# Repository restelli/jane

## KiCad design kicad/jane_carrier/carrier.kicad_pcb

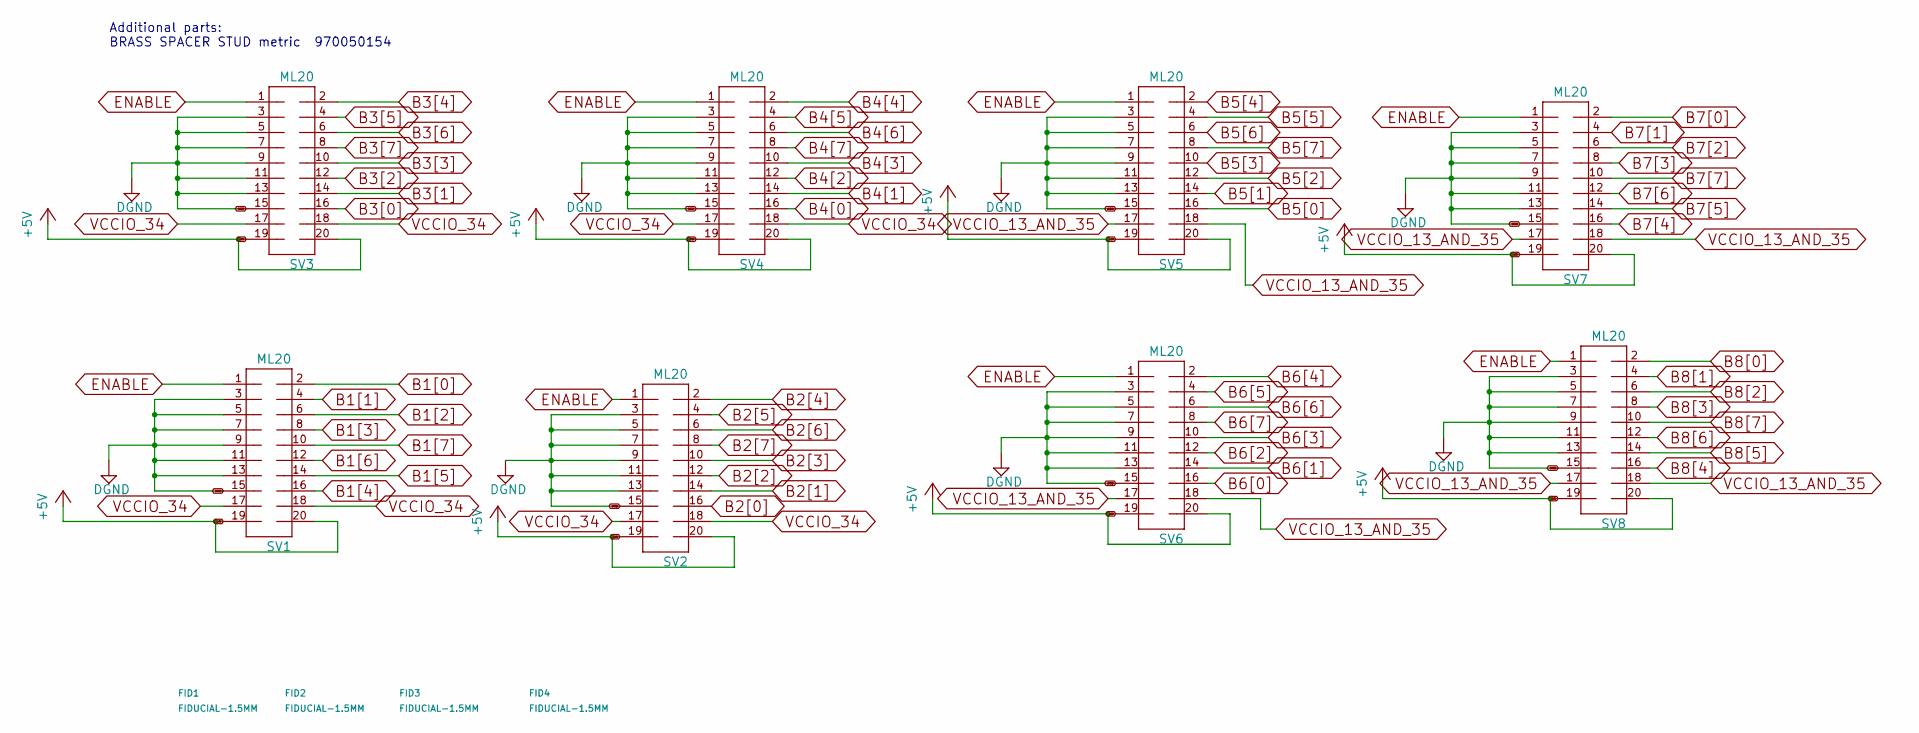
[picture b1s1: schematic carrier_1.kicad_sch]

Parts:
FID1, FID2, FID3, FID4: FIDUCIAL-1.5MM; FID_1.5MM
SV1, SV2, SV3, SV4, SV5, SV6, SV7, SV8: ML20; PARTNO 302-S201; DIGIKEY ED10524-ND

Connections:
+5V: SV1.19, SV1.20, SV2.19, SV2.20, SV3.19, SV3.20, SV4.19, SV4.20, SV5.19, SV5.20, SV6.19, SV6.20, SV7.19, SV7.20, SV8.19, SV8.20; also elsewhere on the board
B1[0]: SV1.2; also elsewhere on the board
B1[1]: SV1.4; also elsewhere on the board
B1[2]: SV1.6; also elsewhere on the board
B1[3]: SV1.8; also elsewhere on the board
B1[4]: SV1.16; also elsewhere on the board
B1[5]: SV1.14; also elsewhere on the board
B1[6]: SV1.12; also elsewhere on the board
B1[7]: SV1.10; also elsewhere on the board
B2[0]: SV2.16; also elsewhere on the board
B2[1]: SV2.14; also elsewhere on the board
B2[2]: SV2.12; also elsewhere on the board
B2[3]: SV2.10; also elsewhere on the board
B2[4]: SV2.2; also elsewhere on the board
B2[5]: SV2.4; also elsewhere on the board
B2[6]: SV2.6; also elsewhere on the board
B2[7]: SV2.8; also elsewhere on the board
B3[0]: SV3.16; also elsewhere on the board
B3[1]: SV3.14; also elsewhere on the board
B3[2]: SV3.12; also elsewhere on the board
B3[3]: SV3.10; also elsewhere on the board
B3[4]: SV3.2; also elsewhere on the board
B3[5]: SV3.4; also elsewhere on the board
B3[6]: SV3.6; also elsewhere on the board
B3[7]: SV3.8; also elsewhere on the board
B4[0]: SV4.16; also elsewhere on the board
B4[1]: SV4.14; also elsewhere on the board
B4[2]: SV4.12; also elsewhere on the board
B4[3]: SV4.10; also elsewhere on the board
B4[4]: SV4.2; also elsewhere on the board
B4[5]: SV4.4; also elsewhere on the board
B4[6]: SV4.6; also elsewhere on the board
B4[7]: SV4.8; also elsewhere on the board
B5[0]: SV5.16; also elsewhere on the board
B5[1]: SV5.14; also elsewhere on the board
B5[2]: SV5.12; also elsewhere on the board
B5[3]: SV5.10; also elsewhere on the board
B5[4]: SV5.2; also elsewhere on the board
B5[5]: SV5.4; also elsewhere on the board
B5[6]: SV5.6; also elsewhere on the board
B5[7]: SV5.8; also elsewhere on the board
B6[0]: SV6.16; also elsewhere on the board
B6[1]: SV6.14; also elsewhere on the board
B6[2]: SV6.12; also elsewhere on the board
B6[3]: SV6.10; also elsewhere on the board
B6[4]: SV6.2; also elsewhere on the board
B6[5]: SV6.4; also elsewhere on the board
B6[6]: SV6.6; also elsewhere on the board
B6[7]: SV6.8; also elsewhere on the board
B7[0]: SV7.2; also elsewhere on the board
B7[1]: SV7.4; also elsewhere on the board
B7[2]: SV7.6; also elsewhere on the board
B7[3]: SV7.8; also elsewhere on the board
B7[4]: SV7.16; also elsewhere on the board
B7[5]: SV7.14; also elsewhere on the board
B7[6]: SV7.12; also elsewhere on the board
B7[7]: SV7.10; also elsewhere on the board
B8[0]: SV8.2; also elsewhere on the board
B8[1]: SV8.4; also elsewhere on the board
B8[2]: SV8.6; also elsewhere on the board
B8[3]: SV8.8; also elsewhere on the board
B8[4]: SV8.16; also elsewhere on the board
B8[5]: SV8.14; also elsewhere on the board
B8[6]: SV8.12; also elsewhere on the board
B8[7]: SV8.10; also elsewhere on the board
DGND: SV1.3, SV1.5, SV1.7, SV1.9, SV1.11, SV1.13, SV1.15, SV2.3, SV2.5, SV2.7, SV2.9, SV2.11, SV2.13, SV2.15, SV3.3, SV3.5, SV3.7, SV3.9, SV3.11, SV3.13, SV3.15, SV4.3, SV4.5, SV4.7, SV4.9, SV4.11, SV4.13, SV4.15, SV5.3, SV5.5, SV5.7, SV5.9, SV5.11, SV5.13, SV5.15, SV6.3, SV6.5, SV6.7, SV6.9, SV6.11, SV6.13, SV6.15, SV7.3, SV7.5, SV7.7, SV7.9, SV7.11, SV7.13, SV7.15, SV8.3, SV8.5, SV8.7, SV8.9, SV8.11, SV8.13, SV8.15; also elsewhere on the board
ENABLE: SV1.1, SV2.1, SV3.1, SV4.1, SV5.1, SV6.1, SV7.1, SV8.1; also elsewhere on the board
VCCIO_13_AND_35: SV5.17, SV5.18, SV6.17, SV6.18, SV7.17, SV7.18, SV8.17, SV8.18; also elsewhere on the board
VCCIO_34: SV1.17, SV1.18, SV2.17, SV2.18, SV3.17, SV3.18, SV4.17, SV4.18; also elsewhere on the board

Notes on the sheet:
Additional parts: BRASS SPACER STUD metric 970050154

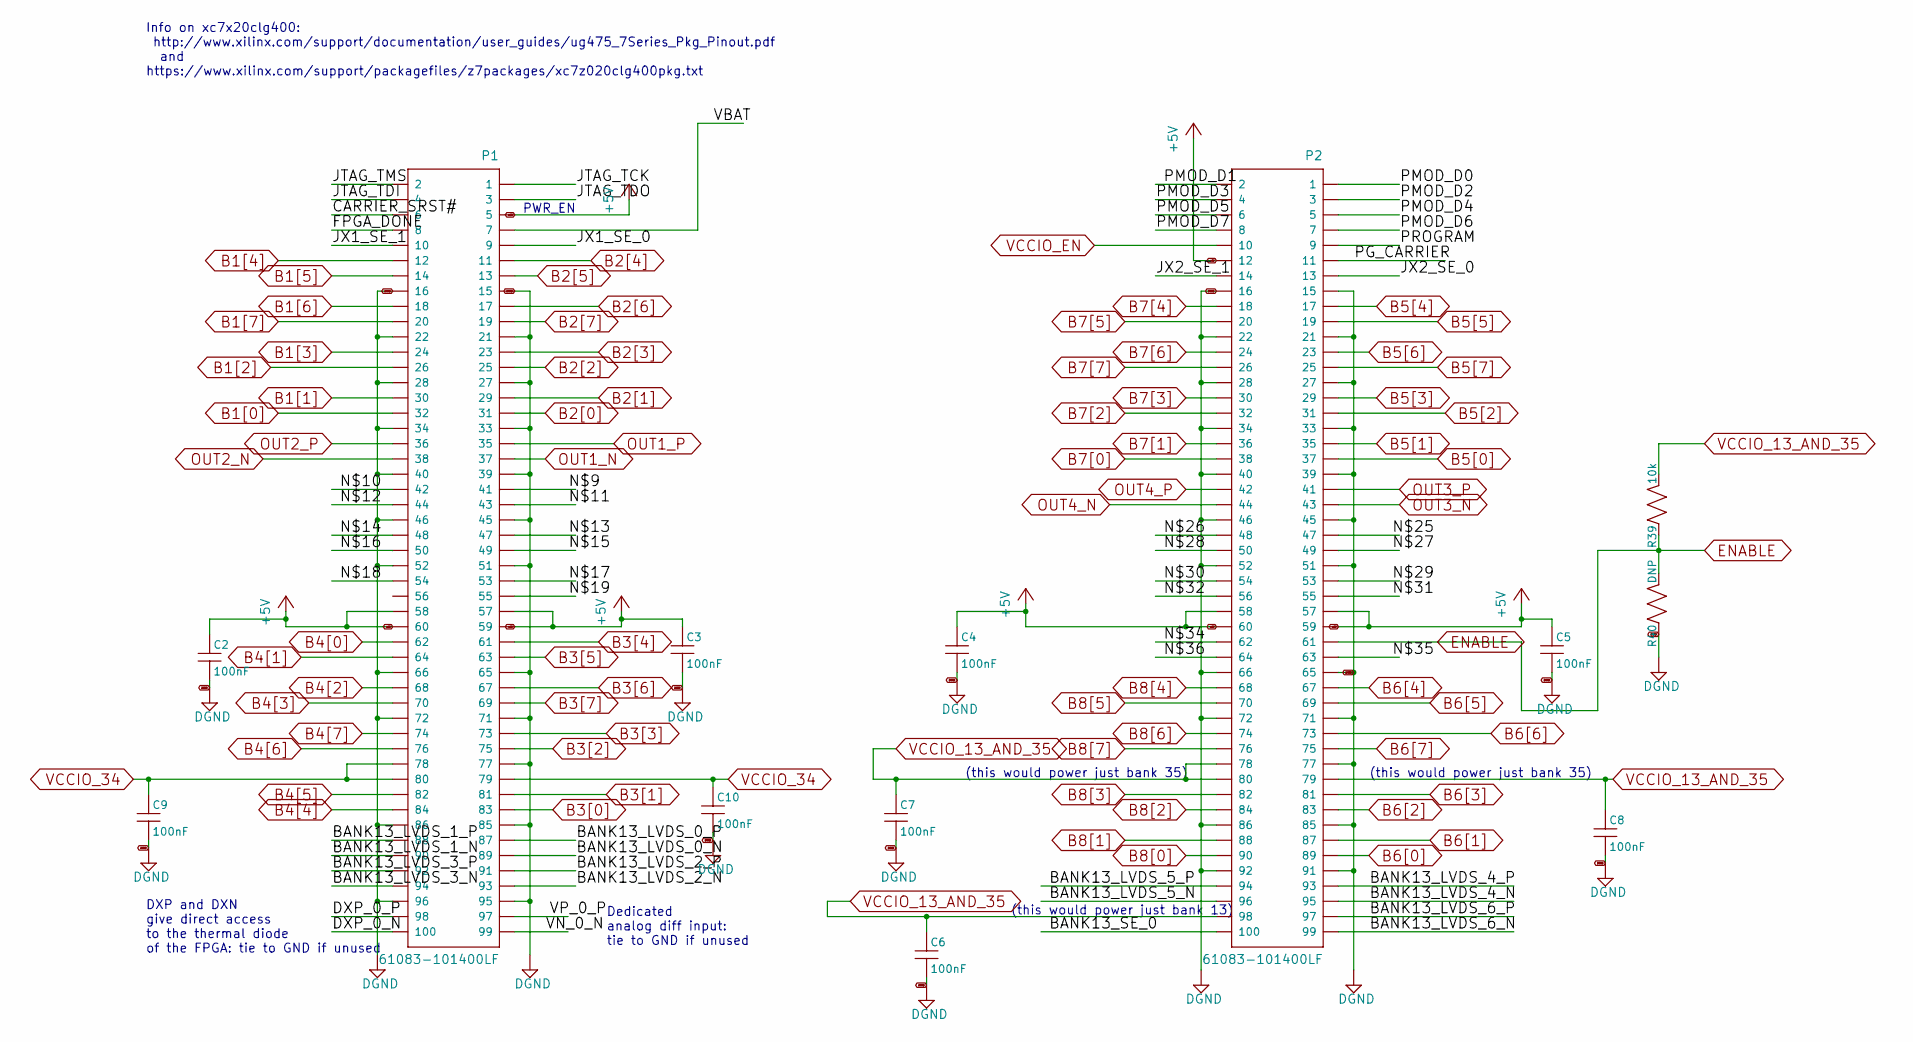
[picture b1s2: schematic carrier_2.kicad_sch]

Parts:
C2, C3, C4, C5, C6, C7, C8, C9, C10: 100nF; C_MLCC_0603; PARTNO AVX 06035C104K4T2A
P1, P2: 61083-101400LF; FCI_61083-101400LF; PARTNO 61083-101400LF
R39: 10k; R_0603; PARTNO ERA-3AED103V
R40: DNP; R_0603

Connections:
+5V: C2.P$1 (1), C3.P$1 (1), C4.P$1 (1), C5.P$1 (1), P1.5, P1.57, P1.58, P1.59, P1.60, P2.12, P2.57, P2.58, P2.59, P2.60; also elsewhere on the board
/carrier_2/BANK13_LVDS_0_N: P1.89
/carrier_2/BANK13_LVDS_0_P: P1.87
/carrier_2/BANK13_LVDS_1_N: P1.90
/carrier_2/BANK13_LVDS_1_P: P1.88
/carrier_2/BANK13_LVDS_2_N: P1.93
/carrier_2/BANK13_LVDS_2_P: P1.91
/carrier_2/BANK13_LVDS_3_N: P1.94
/carrier_2/BANK13_LVDS_3_P: P1.92
/carrier_2/BANK13_LVDS_4_N: P2.95
/carrier_2/BANK13_LVDS_4_P: P2.93
/carrier_2/BANK13_LVDS_5_N: P2.96
/carrier_2/BANK13_LVDS_5_P: P2.94
/carrier_2/BANK13_LVDS_6_N: P2.99
/carrier_2/BANK13_LVDS_6_P: P2.97
/carrier_2/BANK13_SE_0: P2.100
/carrier_2/CARRIER_SRST#: P1.6
/carrier_2/DXP_0_N: P1.100
/carrier_2/DXP_0_P: P1.98
/carrier_2/FPGA_DONE: P1.8
/carrier_2/JTAG_TCK: P1.1
/carrier_2/JTAG_TDI: P1.4
/carrier_2/JTAG_TDO: P1.3
/carrier_2/JTAG_TMS: P1.2
/carrier_2/JX1_SE_0: P1.9
/carrier_2/JX1_SE_1: P1.10
/carrier_2/JX2_SE_0: P2.13
/carrier_2/JX2_SE_1: P2.14
/carrier_2/N$9: P1.41
/carrier_2/N$10: P1.42
/carrier_2/N$11: P1.43
/carrier_2/N$12: P1.44
/carrier_2/N$13: P1.47
/carrier_2/N$14: P1.48
/carrier_2/N$15: P1.49
/carrier_2/N$16: P1.50
/carrier_2/N$17: P1.53
/carrier_2/N$18: P1.54
/carrier_2/N$19: P1.55
/carrier_2/N$25: P2.47
/carrier_2/N$26: P2.48
/carrier_2/N$27: P2.49
/carrier_2/N$28: P2.50
/carrier_2/N$29: P2.53
/carrier_2/N$30: P2.54
/carrier_2/N$31: P2.55
/carrier_2/N$32: P2.56
/carrier_2/N$34: P2.62
/carrier_2/N$35: P2.63
/carrier_2/N$36: P2.64
/carrier_2/PG_CARRIER: P2.11
/carrier_2/PMOD_D0: P2.1
/carrier_2/PMOD_D1: P2.2
/carrier_2/PMOD_D2: P2.3
/carrier_2/PMOD_D3: P2.4
/carrier_2/PMOD_D4: P2.5
/carrier_2/PMOD_D5: P2.6
/carrier_2/PMOD_D6: P2.7
/carrier_2/PMOD_D7: P2.8
/carrier_2/PROGRAM: P2.9
/carrier_2/VBAT: P1.7
/carrier_2/VN_0_N: P1.99
/carrier_2/VP_0_P: P1.97
B1[0]: P1.32; also elsewhere on the board
B1[1]: P1.30; also elsewhere on the board
B1[2]: P1.26; also elsewhere on the board
B1[3]: P1.24; also elsewhere on the board
B1[4]: P1.12; also elsewhere on the board
B1[5]: P1.14; also elsewhere on the board
B1[6]: P1.18; also elsewhere on the board
B1[7]: P1.20; also elsewhere on the board
B2[0]: P1.31; also elsewhere on the board
B2[1]: P1.29; also elsewhere on the board
B2[2]: P1.25; also elsewhere on the board
B2[3]: P1.23; also elsewhere on the board
B2[4]: P1.11; also elsewhere on the board
B2[5]: P1.13; also elsewhere on the board
B2[6]: P1.17; also elsewhere on the board
B2[7]: P1.19; also elsewhere on the board
B3[0]: P1.83; also elsewhere on the board
B3[1]: P1.81; also elsewhere on the board
B3[2]: P1.75; also elsewhere on the board
B3[3]: P1.73; also elsewhere on the board
B3[4]: P1.61; also elsewhere on the board
B3[5]: P1.63; also elsewhere on the board
B3[6]: P1.67; also elsewhere on the board
B3[7]: P1.69; also elsewhere on the board
B4[0]: P1.62; also elsewhere on the board
B4[1]: P1.64; also elsewhere on the board
B4[2]: P1.68; also elsewhere on the board
B4[3]: P1.70; also elsewhere on the board
B4[4]: P1.84; also elsewhere on the board
B4[5]: P1.82; also elsewhere on the board
B4[6]: P1.76; also elsewhere on the board
B4[7]: P1.74; also elsewhere on the board
B5[0]: P2.37; also elsewhere on the board
B5[1]: P2.35; also elsewhere on the board
B5[2]: P2.31; also elsewhere on the board
B5[3]: P2.29; also elsewhere on the board
B5[4]: P2.17; also elsewhere on the board
B5[5]: P2.19; also elsewhere on the board
B5[6]: P2.23; also elsewhere on the board
B5[7]: P2.25; also elsewhere on the board
B6[0]: P2.89; also elsewhere on the board
B6[1]: P2.87; also elsewhere on the board
B6[2]: P2.83; also elsewhere on the board
B6[3]: P2.81; also elsewhere on the board
B6[4]: P2.67; also elsewhere on the board
B6[5]: P2.69; also elsewhere on the board
B6[6]: P2.73; also elsewhere on the board
B6[7]: P2.75; also elsewhere on the board
B7[0]: P2.38; also elsewhere on the board
B7[1]: P2.36; also elsewhere on the board
B7[2]: P2.32; also elsewhere on the board
B7[3]: P2.30; also elsewhere on the board
B7[4]: P2.18; also elsewhere on the board
B7[5]: P2.20; also elsewhere on the board
B7[6]: P2.24; also elsewhere on the board
B7[7]: P2.26; also elsewhere on the board
B8[0]: P2.90; also elsewhere on the board
B8[1]: P2.88; also elsewhere on the board
B8[2]: P2.84; also elsewhere on the board
B8[3]: P2.82; also elsewhere on the board
B8[4]: P2.68; also elsewhere on the board
B8[5]: P2.70; also elsewhere on the board
B8[6]: P2.74; also elsewhere on the board
B8[7]: P2.76; also elsewhere on the board
DGND: C2.P$2 (2), C3.P$2 (2), C4.P$2 (2), C5.P$2 (2), C6.P$2 (2), C7.P$2 (2), C8.P$2 (2), C9.P$2 (2), C10.P$2 (2), P1.15, P1.16, P1.21, P1.22, P1.27, P1.28, P1.33, P1.34, P1.39, P1.40, P1.45, P1.46, P1.51, P1.52, P1.65, P1.66, P1.71, P1.72, P1.77, P1.85, P1.86, P1.95, P1.96, P2.15, P2.16, P2.21, P2.22, P2.27, P2.28, P2.33, P2.34, P2.39, P2.40, P2.45, P2.46, P2.51, P2.52, P2.65, P2.66, P2.71, P2.72, P2.77, P2.85, P2.86, P2.91, P2.92, R40.P$1 (1); also elsewhere on the board
ENABLE: P2.61, R39.P$1 (1), R40.P$2 (2); also elsewhere on the board
OUT1_N: P1.37; also elsewhere on the board
OUT1_P: P1.35; also elsewhere on the board
OUT2_N: P1.38; also elsewhere on the board
OUT2_P: P1.36; also elsewhere on the board
OUT3_N: P2.43; also elsewhere on the board
OUT3_P: P2.41; also elsewhere on the board
OUT4_N: P2.44; also elsewhere on the board
OUT4_P: P2.42; also elsewhere on the board
VCCIO_13_AND_35: C6.P$1 (1), C7.P$1 (1), C8.P$1 (1), P2.78, P2.79, P2.80, P2.98, R39.P$2 (2); also elsewhere on the board
VCCIO_34: C9.P$1 (1), C10.P$1 (1), P1.78, P1.79, P1.80; also elsewhere on the board
VCCIO_EN: P2.10; also elsewhere on the board

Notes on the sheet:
Dedicated analog diff input: tie to GND if unused
(this would power just bank 13)
(this would power just bank 35)
DXP and DXN give direct access to the thermal diode of the FPGA: tie to GND if unused
Info on xc7x20clg400: http://www.xilinx.com/support/documentation/user_guides/ug475_7Series_Pkg_Pinout.pdf and https://www.xilinx.com/support/packagefiles/z7packages/xc7z020clg400pkg.txt
PWR_EN

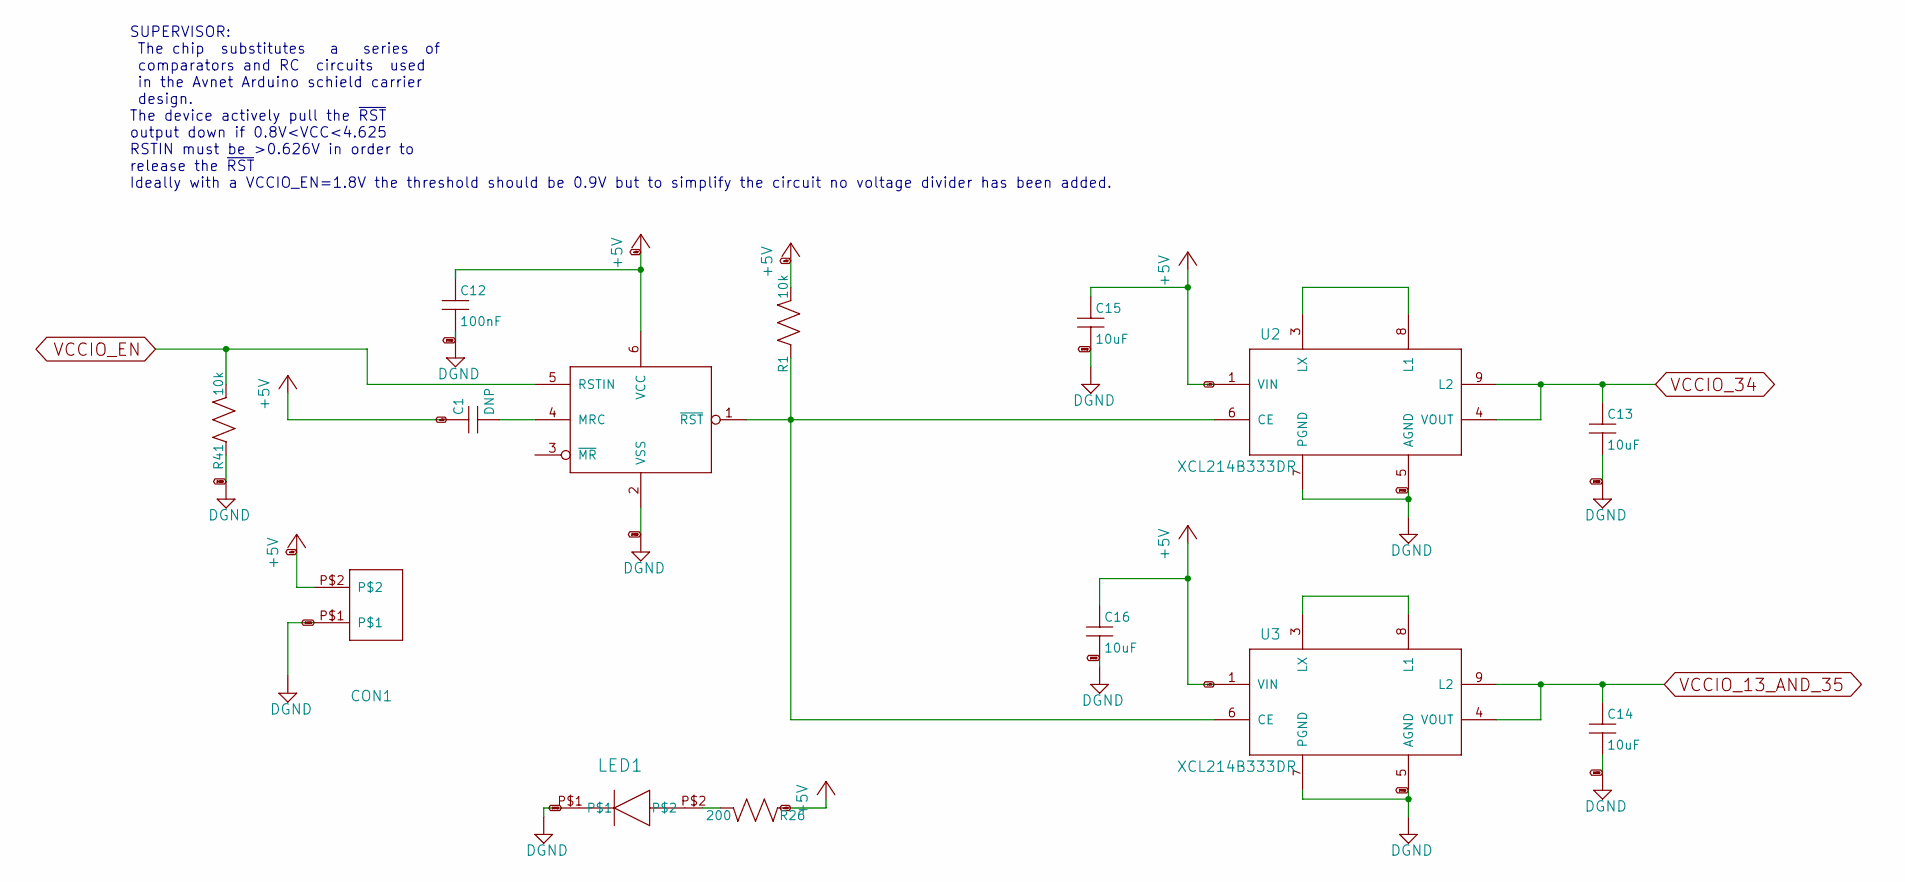
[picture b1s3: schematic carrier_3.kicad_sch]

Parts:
C1: DNP; C_MLCC_0603
C12: 100nF; C_MLCC_0603; PARTNO AVX 06035C104K4T2A
C13, C14, C15, C16: 10uF; C_MLCC_1210; PARTNO TDK C3225X5R1E106K250AA
CON1: EDSTL130_02
LED1: LED-AA4040QBS; PARTNO AA4040QBS/D
R1, R41: 10k; R_0603; PARTNO ERA-3AED103V
R26: 200; R_0603; PARTNO CRCW0603200RFKEA
U1: STM6779LWB6F; SOT95P280X145-6N; PARTNO STM6779LWB6F; DIGIKEY 497-8008-1-ND
U2, U3: XCL214B333DR; TOREX_XCL214B123DR; PARTNO XCL214B333DR; DIGIKEY 893-1218-1-ND

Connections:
+5V: C1.P$1 (1), C12.P$1 (1), C15.P$1 (1), C16.P$1 (1), CON1.P$2, R1.P$2 (2), R26.P$1 (1), U1.6 (VCC), U2.1 (VIN), U3.1 (VIN); also elsewhere on the board
DGND: C12.P$2 (2), C13.P$2 (2), C14.P$2 (2), C15.P$2 (2), C16.P$2 (2), CON1.P$1, LED1.P$1, R41.P$1 (1), U1.2 (VSS), U2.5 (AGND), U2.7 (PGND), U3.5 (AGND), U3.7 (PGND); also elsewhere on the board
unnamed: C1.P$2 (2), U1.4 (MRC)
unnamed: LED1.P$2, R26.P$2 (2)
unnamed: R1.P$1 (1), U1.1 (~RST), U2.6 (CE), U3.6 (CE)
unnamed: U2.3 (LX), U2.8 (L1)
unnamed: U3.3 (LX), U3.8 (L1)
VCCIO_13_AND_35: C14.P$1 (1), U3.4 (VOUT), U3.9 (L2); also elsewhere on the board
VCCIO_34: C13.P$1 (1), U2.4 (VOUT), U2.9 (L2); also elsewhere on the board
VCCIO_EN: R41.P$2 (2), U1.5 (RSTIN); also elsewhere on the board

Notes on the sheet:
SUPERVISOR: The chip substitutes a series of comparators and RC circuits used in the Avnet Arduino schield carrier design. The device actively pull the ~{RST} output down if 0.8V<VCC<4.625 RSTIN must be >0.626V in order to release the ~{RST} Ideally with a VCCIO_EN=1.8V the threshold should be 0.9V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

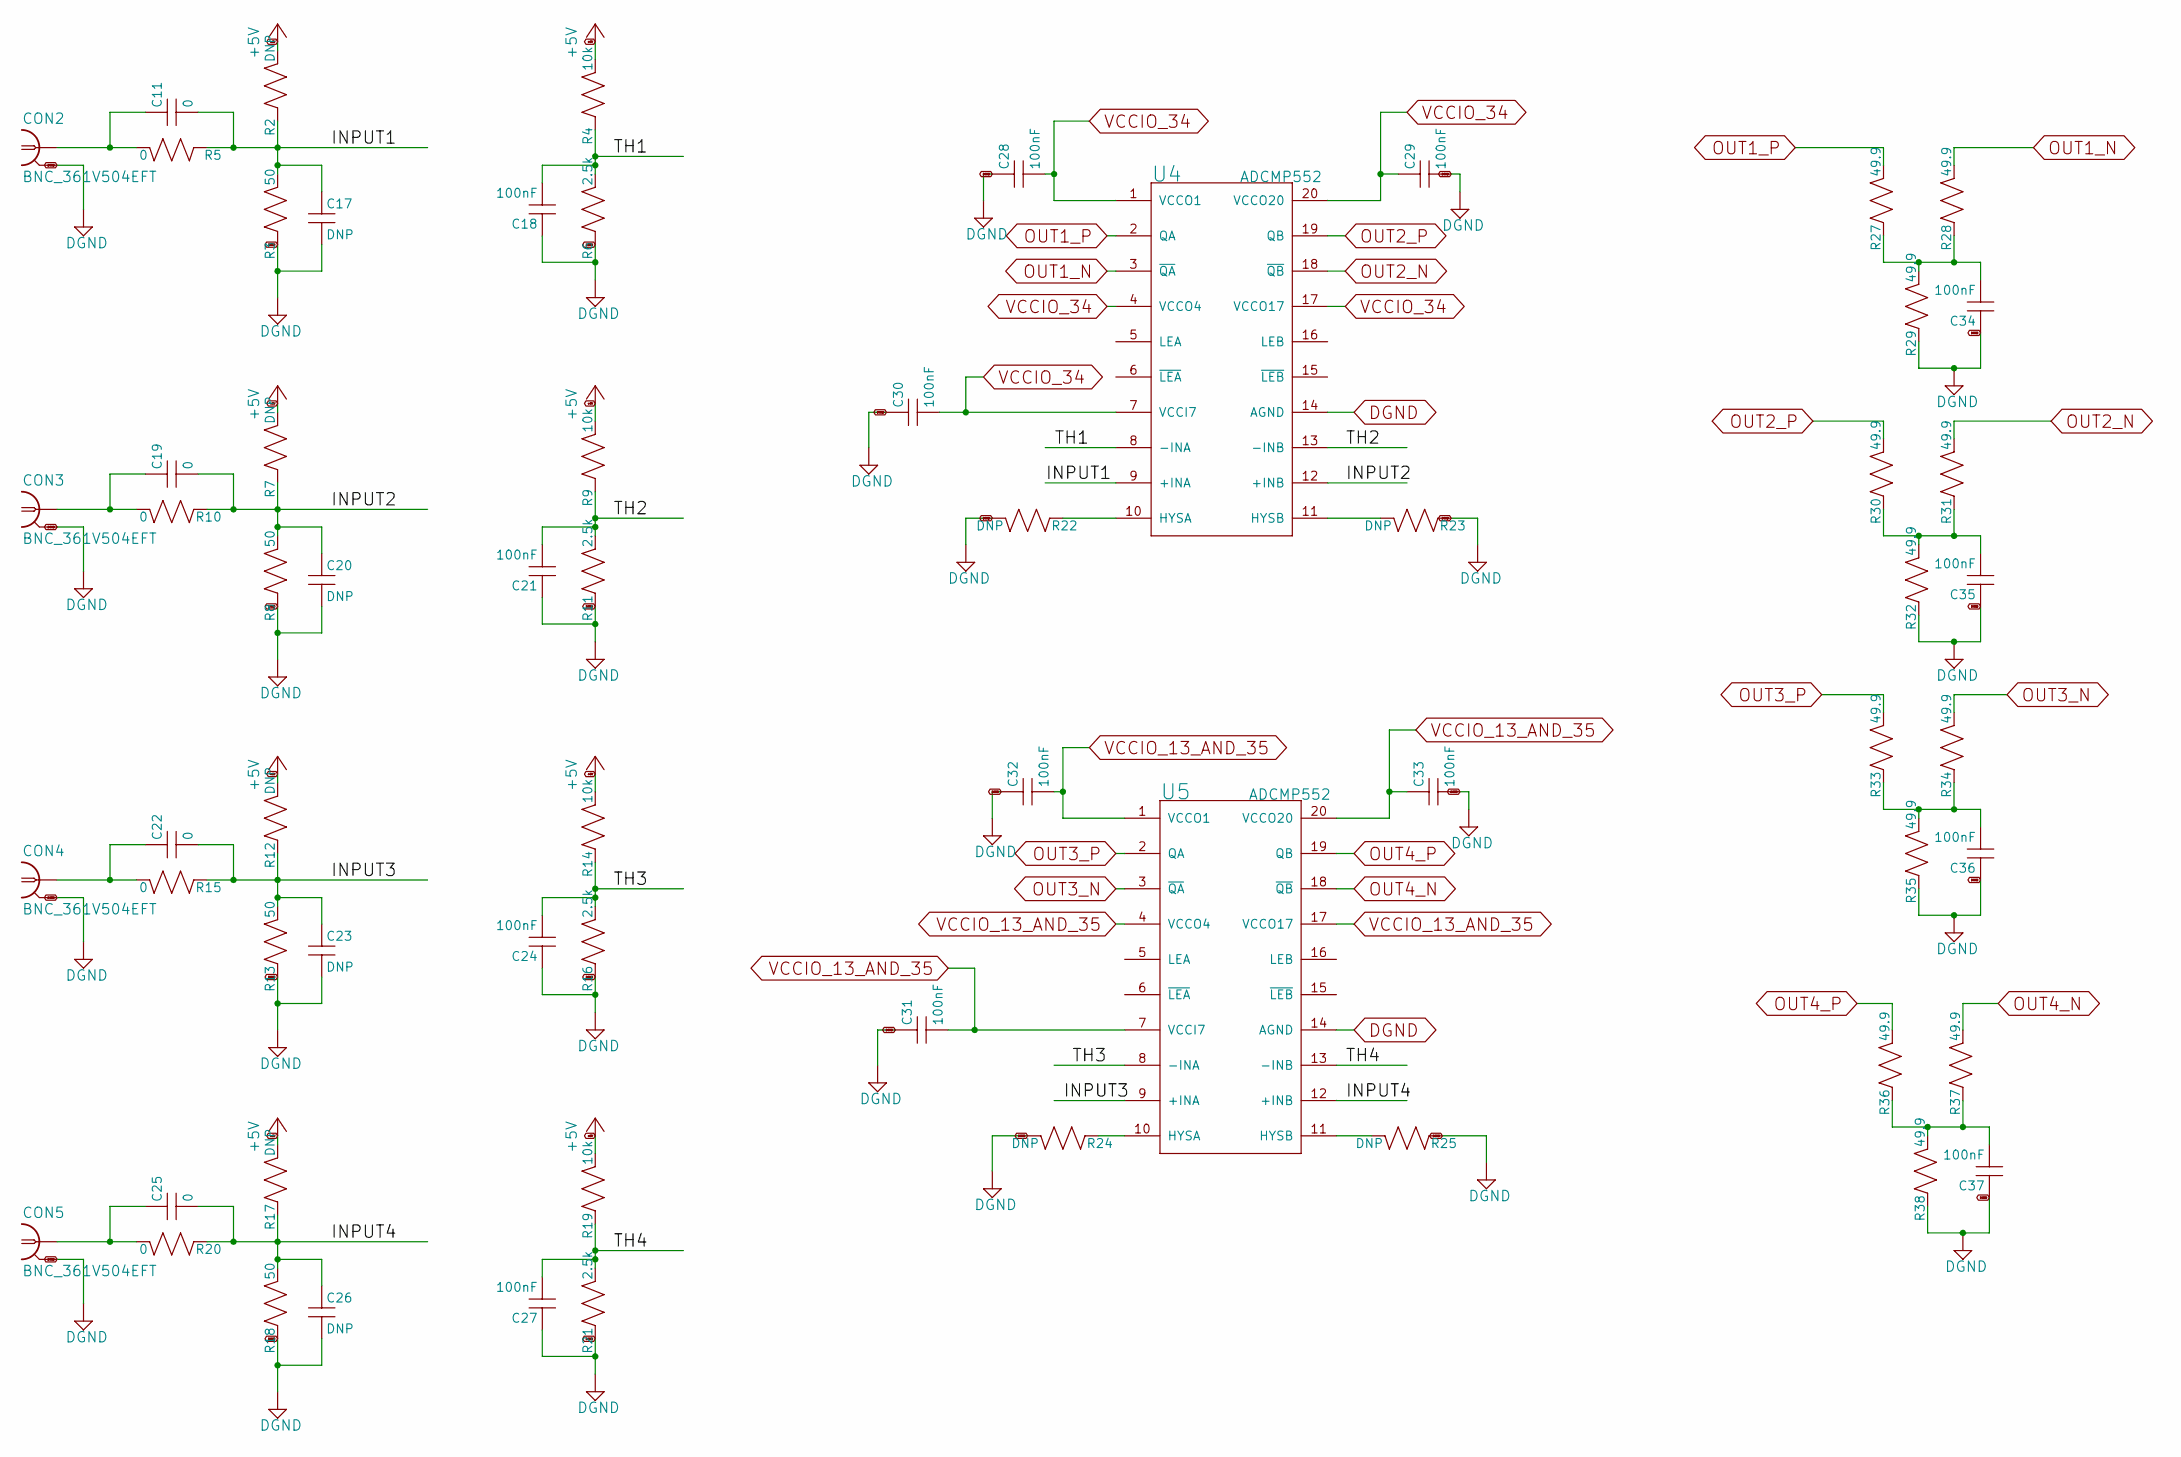
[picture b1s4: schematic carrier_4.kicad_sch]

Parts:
C11, C19, C22, C25: 0; C_MLCC_0603; PARTNO MF-RES-0603-0
C17, C20, C23, C26: DNP; C_MLCC_0603
C18, C21, C24, C27, C28, C29, C30, C31, C32, C33, C34, C35, C36, C37: 100nF; C_MLCC_0603; PARTNO AVX 06035C104K4T2A
CON2, CON3, CON4, CON5: BNC_361V504EFT; BNC_V-BITE_PCB_EDGE; PARTNO 361V504EFT; DIGIKEY 991-1035-ND
R2, R7, R12, R17, R22, R23, R24, R25: DNP; R_0603
R3, R8, R13, R18: 50; R_0603; PARTNO PCAN0603E49R9BST5; DIGIKEY 764-1250-1-ND
R4, R9, R14, R19: 10k; R_0603; PARTNO ERA-3AED103V
R5, R10, R15, R20: 0; R_0603; PARTNO MF-RES-0603-0
R6, R11, R16, R21: 2.5k; R_0603; PARTNO ERA3ARB2491V
R27, R28, R29, R30, R31, R32, R33, R34, R35, R36, R37, R38: 49.9; R_0603; PARTNO RR0816Q-49R9-D-68R; DIGIKEY RR08Q49.9DCT-ND
U4, U5: ADCMP552; QSOP20

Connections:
+5V: R2.P$2 (2), R4.P$2 (2), R7.P$2 (2), R9.P$2 (2), R12.P$2 (2), R14.P$2 (2), R17.P$2 (2), R19.P$2 (2); also elsewhere on the board
/carrier_4/INPUT1: C11.P$2 (2), C17.P$1 (1), R2.P$1 (1), R3.P$2 (2), R5.P$1 (1), U4.9 (+INA)
/carrier_4/INPUT2: C19.P$2 (2), C20.P$1 (1), R7.P$1 (1), R8.P$2 (2), R10.P$1 (1), U4.12 (+INB)
/carrier_4/INPUT3: C22.P$2 (2), C23.P$1 (1), R12.P$1 (1), R13.P$2 (2), R15.P$1 (1), U5.9 (+INA)
/carrier_4/INPUT4: C25.P$2 (2), C26.P$1 (1), R17.P$1 (1), R18.P$2 (2), R20.P$1 (1), U5.12 (+INB)
/carrier_4/TH1: C18.P$2 (2), R4.P$1 (1), R6.P$2 (2), U4.8 (-INA)
/carrier_4/TH2: C21.P$2 (2), R9.P$1 (1), R11.P$2 (2), U4.13 (-INB)
/carrier_4/TH3: C24.P$2 (2), R14.P$1 (1), R16.P$2 (2), U5.8 (-INA)
/carrier_4/TH4: C27.P$2 (2), R19.P$1 (1), R21.P$2 (2), U5.13 (-INB)
DGND: C17.P$2 (2), C18.P$1 (1), C20.P$2 (2), C21.P$1 (1), C23.P$2 (2), C24.P$1 (1), C26.P$2 (2), C27.P$1 (1), C28.P$1 (1), C29.P$2 (2), C30.P$1 (1), C31.P$1 (1), C32.P$1 (1), C33.P$2 (2), C34.P$1 (1), C35.P$1 (1), C36.P$1 (1), C37.P$1 (1), CON2.GND$1 (2), CON2.GND$2 (2), CON3.GND$1 (2), CON3.GND$2 (2), CON4.GND$1 (2), CON4.GND$2 (2), CON5.GND$1 (2), CON5.GND$2 (2), R3.P$1 (1), R6.P$1 (1), R8.P$1 (1), R11.P$1 (1), R13.P$1 (1), R16.P$1 (1), R18.P$1 (1), R21.P$1 (1), R22.P$2 (2), R23.P$1 (1), R24.P$2 (2), R25.P$1 (1), R29.P$1 (1), R32.P$1 (1), R35.P$1 (1), R38.P$1 (1), U4.14 (AGND), U5.14 (AGND); also elsewhere on the board
unnamed: C11.P$1 (1), CON2.P$1 (1), R5.P$2 (2)
unnamed: C19.P$1 (1), CON3.P$1 (1), R10.P$2 (2)
unnamed: C22.P$1 (1), CON4.P$1 (1), R15.P$2 (2)
unnamed: C25.P$1 (1), CON5.P$1 (1), R20.P$2 (2)
unnamed: C34.P$2 (2), R27.P$1 (1), R28.P$1 (1), R29.P$2 (2)
unnamed: C35.P$2 (2), R30.P$1 (1), R31.P$1 (1), R32.P$2 (2)
unnamed: C36.P$2 (2), R33.P$1 (1), R34.P$1 (1), R35.P$2 (2)
unnamed: C37.P$2 (2), R36.P$1 (1), R37.P$1 (1), R38.P$2 (2)
unnamed: R22.P$1 (1), U4.10 (HYSA)
unnamed: R23.P$2 (2), U4.11 (HYSB)
unnamed: R24.P$1 (1), U5.10 (HYSA)
unnamed: R25.P$2 (2), U5.11 (HYSB)
OUT1_N: R28.P$2 (2), U4.3 (~QA); also elsewhere on the board
OUT1_P: R27.P$2 (2), U4.2 (QA); also elsewhere on the board
OUT2_N: R31.P$2 (2), U4.18 (~QB); also elsewhere on the board
OUT2_P: R30.P$2 (2), U4.19 (QB); also elsewhere on the board
OUT3_N: R34.P$2 (2), U5.3 (~QA); also elsewhere on the board
OUT3_P: R33.P$2 (2), U5.2 (QA); also elsewhere on the board
OUT4_N: R37.P$2 (2), U5.18 (~QB); also elsewhere on the board
OUT4_P: R36.P$2 (2), U5.19 (QB); also elsewhere on the board
VCCIO_13_AND_35: C31.P$2 (2), C32.P$2 (2), C33.P$1 (1), U5.1 (VCCO1), U5.4 (VCCO4), U5.7 (VCCI7), U5.17 (VCCO17), U5.20 (VCCO20); also elsewhere on the board
VCCIO_34: C28.P$2 (2), C29.P$1 (1), C30.P$2 (2), U4.1 (VCCO1), U4.4 (VCCO4), U4.7 (VCCI7), U4.17 (VCCO17), U4.20 (VCCO20); also elsewhere on the board

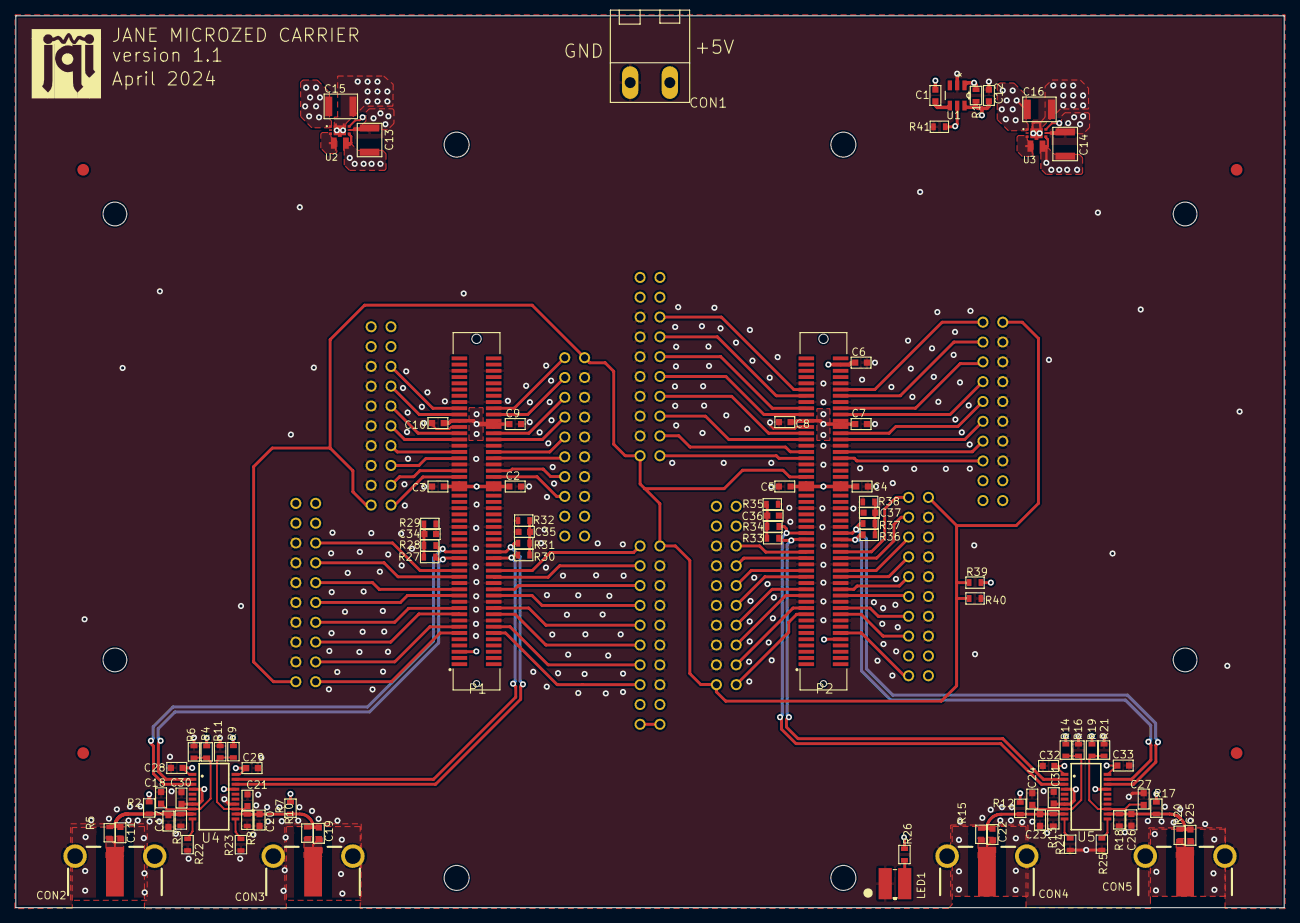
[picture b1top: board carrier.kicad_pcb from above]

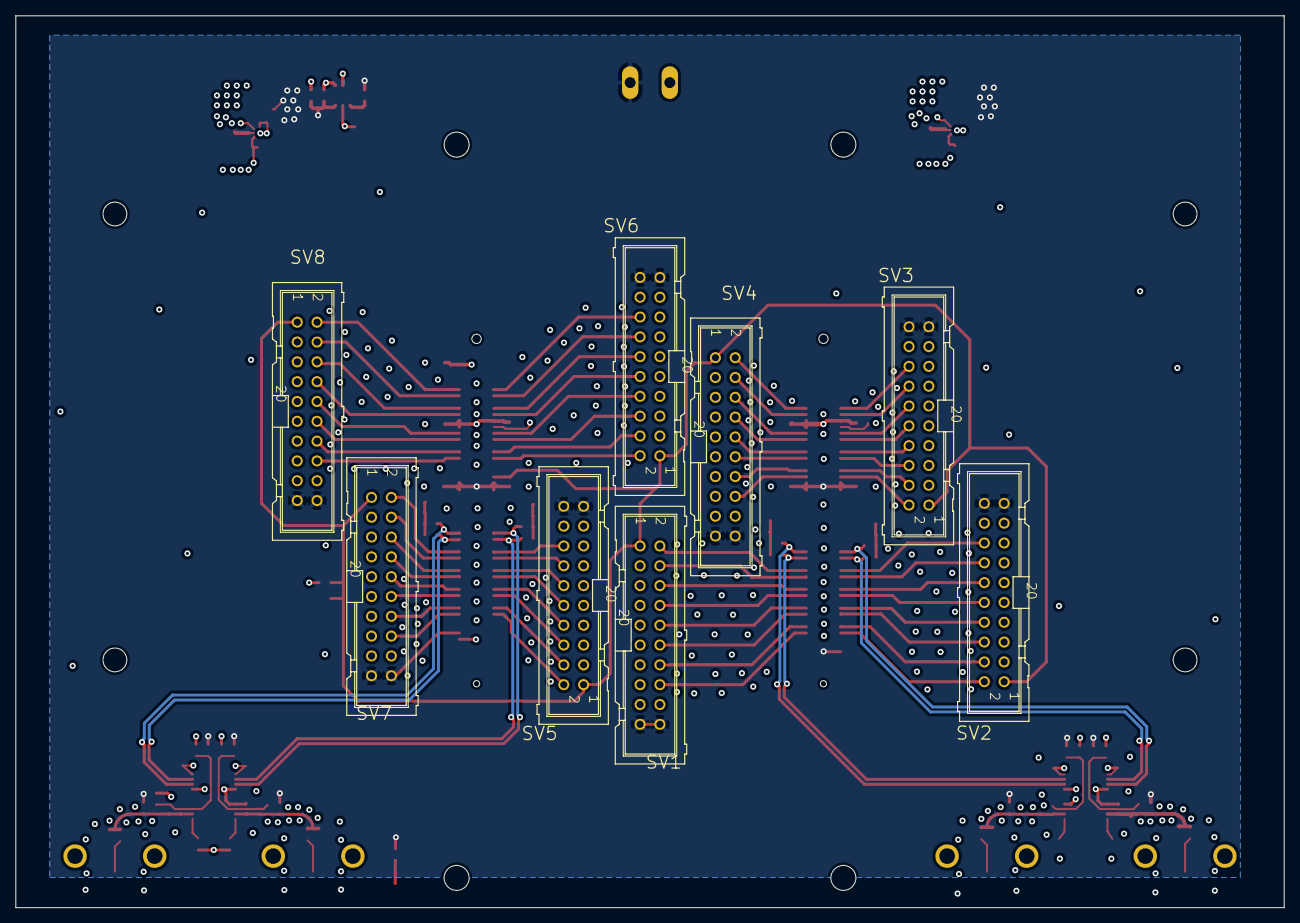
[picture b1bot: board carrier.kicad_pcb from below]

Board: 4 copper layers, 162.6 x 114.3 mm, 112 parts (8 on the bottom side), 103 nets.

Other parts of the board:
@HOLE0, @HOLE1, @HOLE2, @HOLE3, @HOLE4, @HOLE5, @HOLE6, @HOLE7: (no value)
LOGO3: JQI-LOGOSILK; JQI_LOGO_NEGATIVE-SILKSCREEN
